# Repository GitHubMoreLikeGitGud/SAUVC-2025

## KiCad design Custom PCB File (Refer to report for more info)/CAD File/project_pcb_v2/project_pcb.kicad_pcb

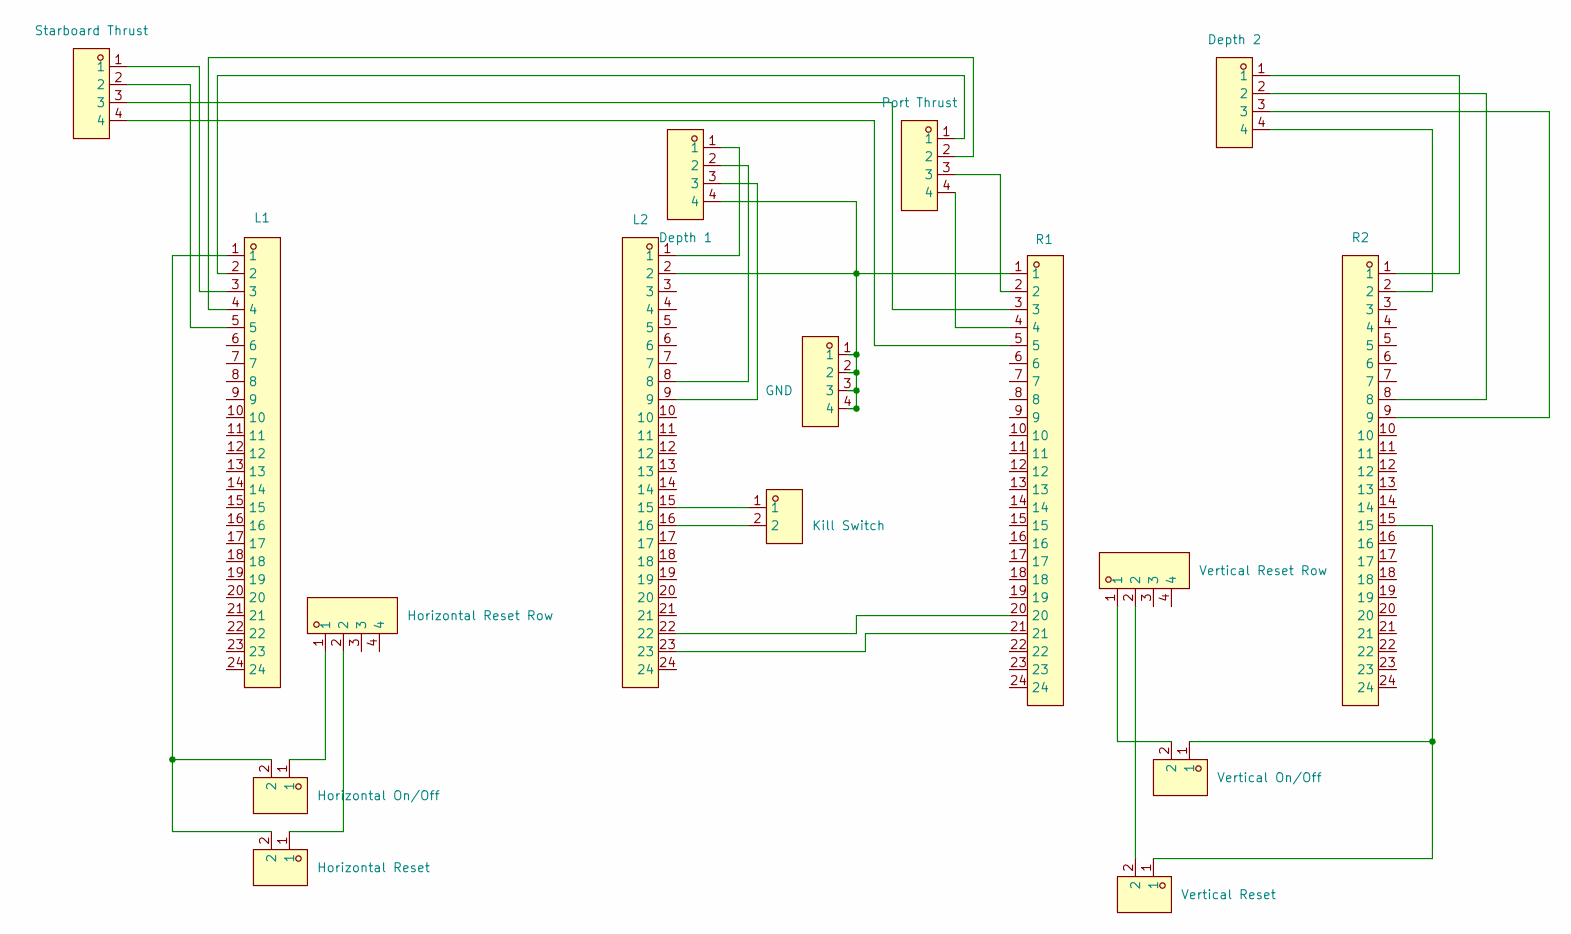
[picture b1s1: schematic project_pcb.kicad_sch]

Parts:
CN1: GND; CONN-TH_4P-P2.54_CAX_2510-4A; LCSC Part C2847671
CN2: Starboard Thrust; CONN-TH_4P-P2.54_CAX_2510-4A; LCSC Part C2847671
CN3: Port Thrust; CONN-TH_4P-P2.54_CAX_2510-4A; LCSC Part C2847671
CN4: Horizontal Reset Row; HDR-TH_4P-P2.54-V-F; LCSC Part C2847671
CN6: Vertical Reset Row; HDR-TH_4P-P2.54-V-F; LCSC Part C2847671
Depth2: Depth 2; HDR-TH_4P-P2.54-V-F; LCSC Part C2718488
H1: Depth 1; HDR-TH_4P-P2.54-V-F; LCSC Part C2718488
Kill_Switch1: Kill Switch; CONN-TH_P5.00_KF128-5.0-2P; LCSC Part C474950
Kill_Switch2: Horizontal Reset; CONN-TH_P5.00_KF128-5.0-2P; LCSC Part C474950
Kill_Switch3: Vertical Reset; CONN-TH_P5.00_KF128-5.0-2P; LCSC Part C474950
Kill_Switch4: Horizontal On/Off; CONN-TH_P5.00_KF128-5.0-2P; LCSC Part C474950
Kill_Switch5: Vertical On/Off; CONN-TH_P5.00_KF128-5.0-2P; LCSC Part C474950
U1: L1; HDR-TH_24P-P2.54-V-F; LCSC Part C2883741
U2: L2; HDR-TH_24P-P2.54-V-F; LCSC Part C2883741
U3: R1; HDR-TH_24P-P2.54-V-F; LCSC Part C2883741
U4: R2; HDR-TH_24P-P2.54-V-F; LCSC Part C2883741

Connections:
unnamed: CN1.1, CN1.2, CN1.3, CN1.4, H1.4, U2.2, U3.1
unnamed: CN2.1, U1.3
unnamed: CN2.2, U1.5
unnamed: CN2.3, U3.3
unnamed: CN2.4, U3.5
unnamed: CN3.1, U1.2
unnamed: CN3.2, U1.4
unnamed: CN3.3, U3.2
unnamed: CN3.4, U3.4
unnamed: CN4.1, Kill_Switch4.1
unnamed: CN4.2, Kill_Switch2.1
unnamed: CN6.1, Kill_Switch5.2
unnamed: CN6.2, Kill_Switch3.2
unnamed: Depth2.1, U4.1
unnamed: Depth2.2, U4.8
unnamed: Depth2.3, U4.9
unnamed: Depth2.4, U4.2
unnamed: H1.1, U2.1
unnamed: H1.2, U2.8
unnamed: H1.3, U2.9
unnamed: Kill_Switch1.1, U2.15
unnamed: Kill_Switch1.2, U2.16
unnamed: Kill_Switch2.2, Kill_Switch4.2, U1.1
unnamed: Kill_Switch3.1, Kill_Switch5.1, U4.15
unnamed: U2.22, U3.20
unnamed: U2.23, U3.21

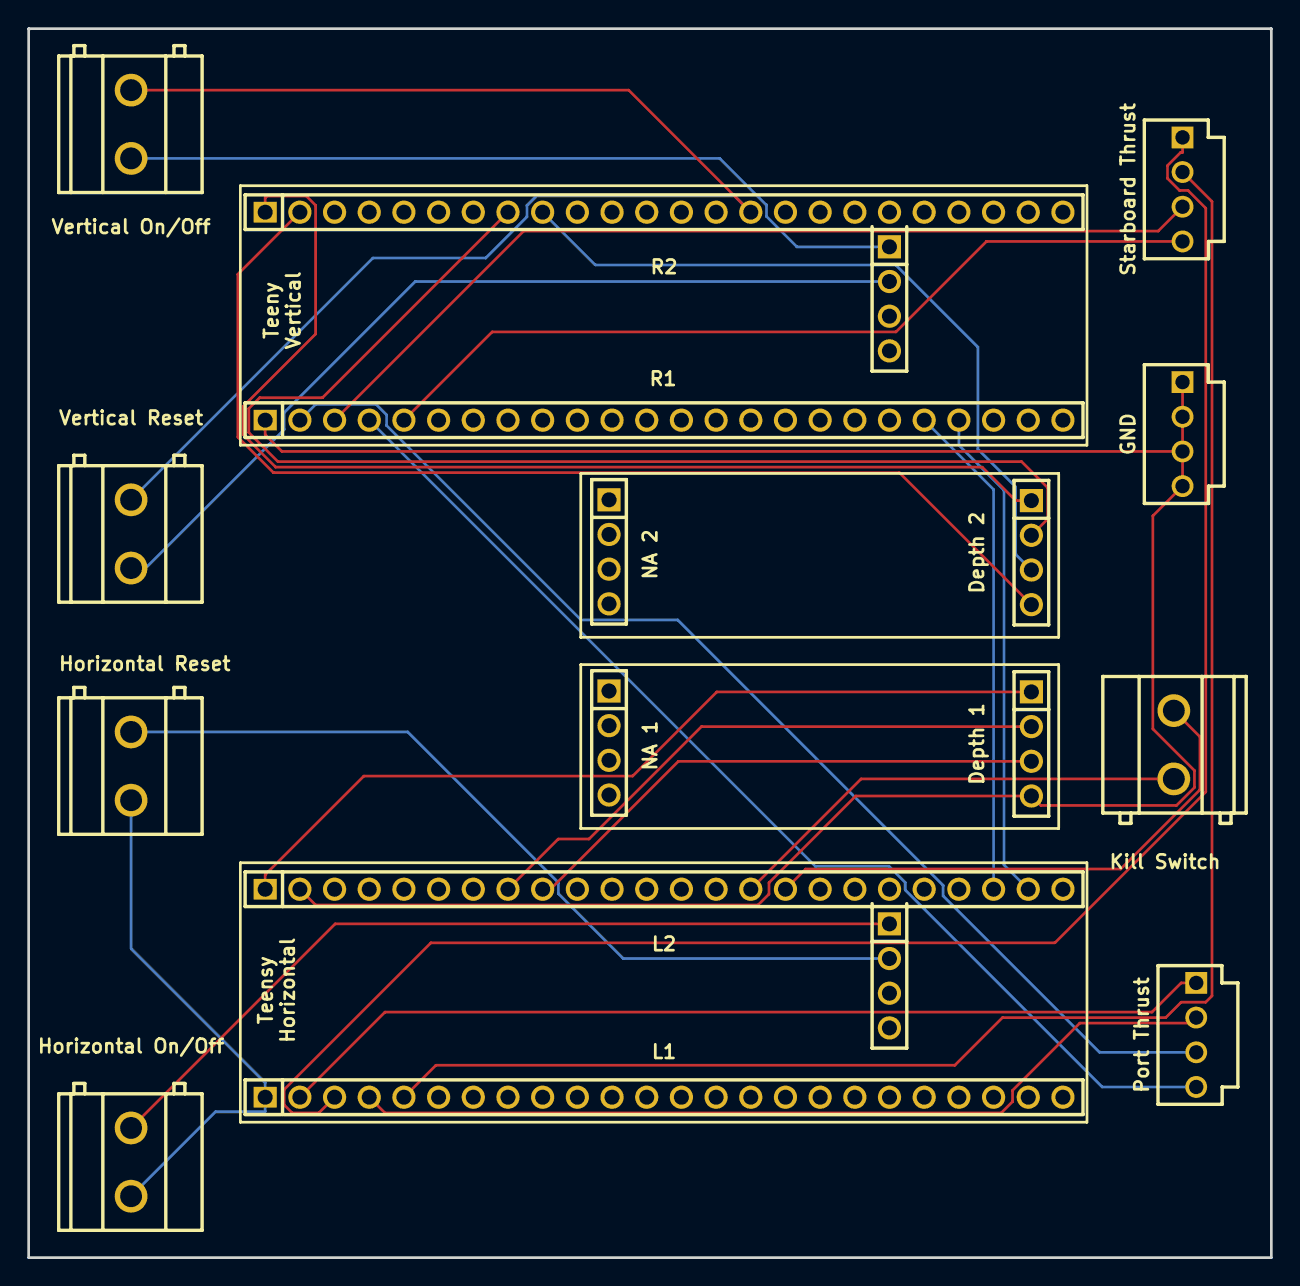
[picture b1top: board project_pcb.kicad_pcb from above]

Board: 2 copper layers, 91.0 x 90.0 mm, 18 parts (0 on the bottom side), 26 nets.

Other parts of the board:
DepthNA1: NA 1; HDR-TH_4P-P2.54-V-F
DepthNA2: NA 2; HDR-TH_4P-P2.54-V-F

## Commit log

2025-03-20 Added Code files
2025-03-20 Added PCB Folder
2025-03-20 Vert New
    for vertical AUV thruster
2025-03-20 Hori gen 2
    Horizontal thrusters for AUV
